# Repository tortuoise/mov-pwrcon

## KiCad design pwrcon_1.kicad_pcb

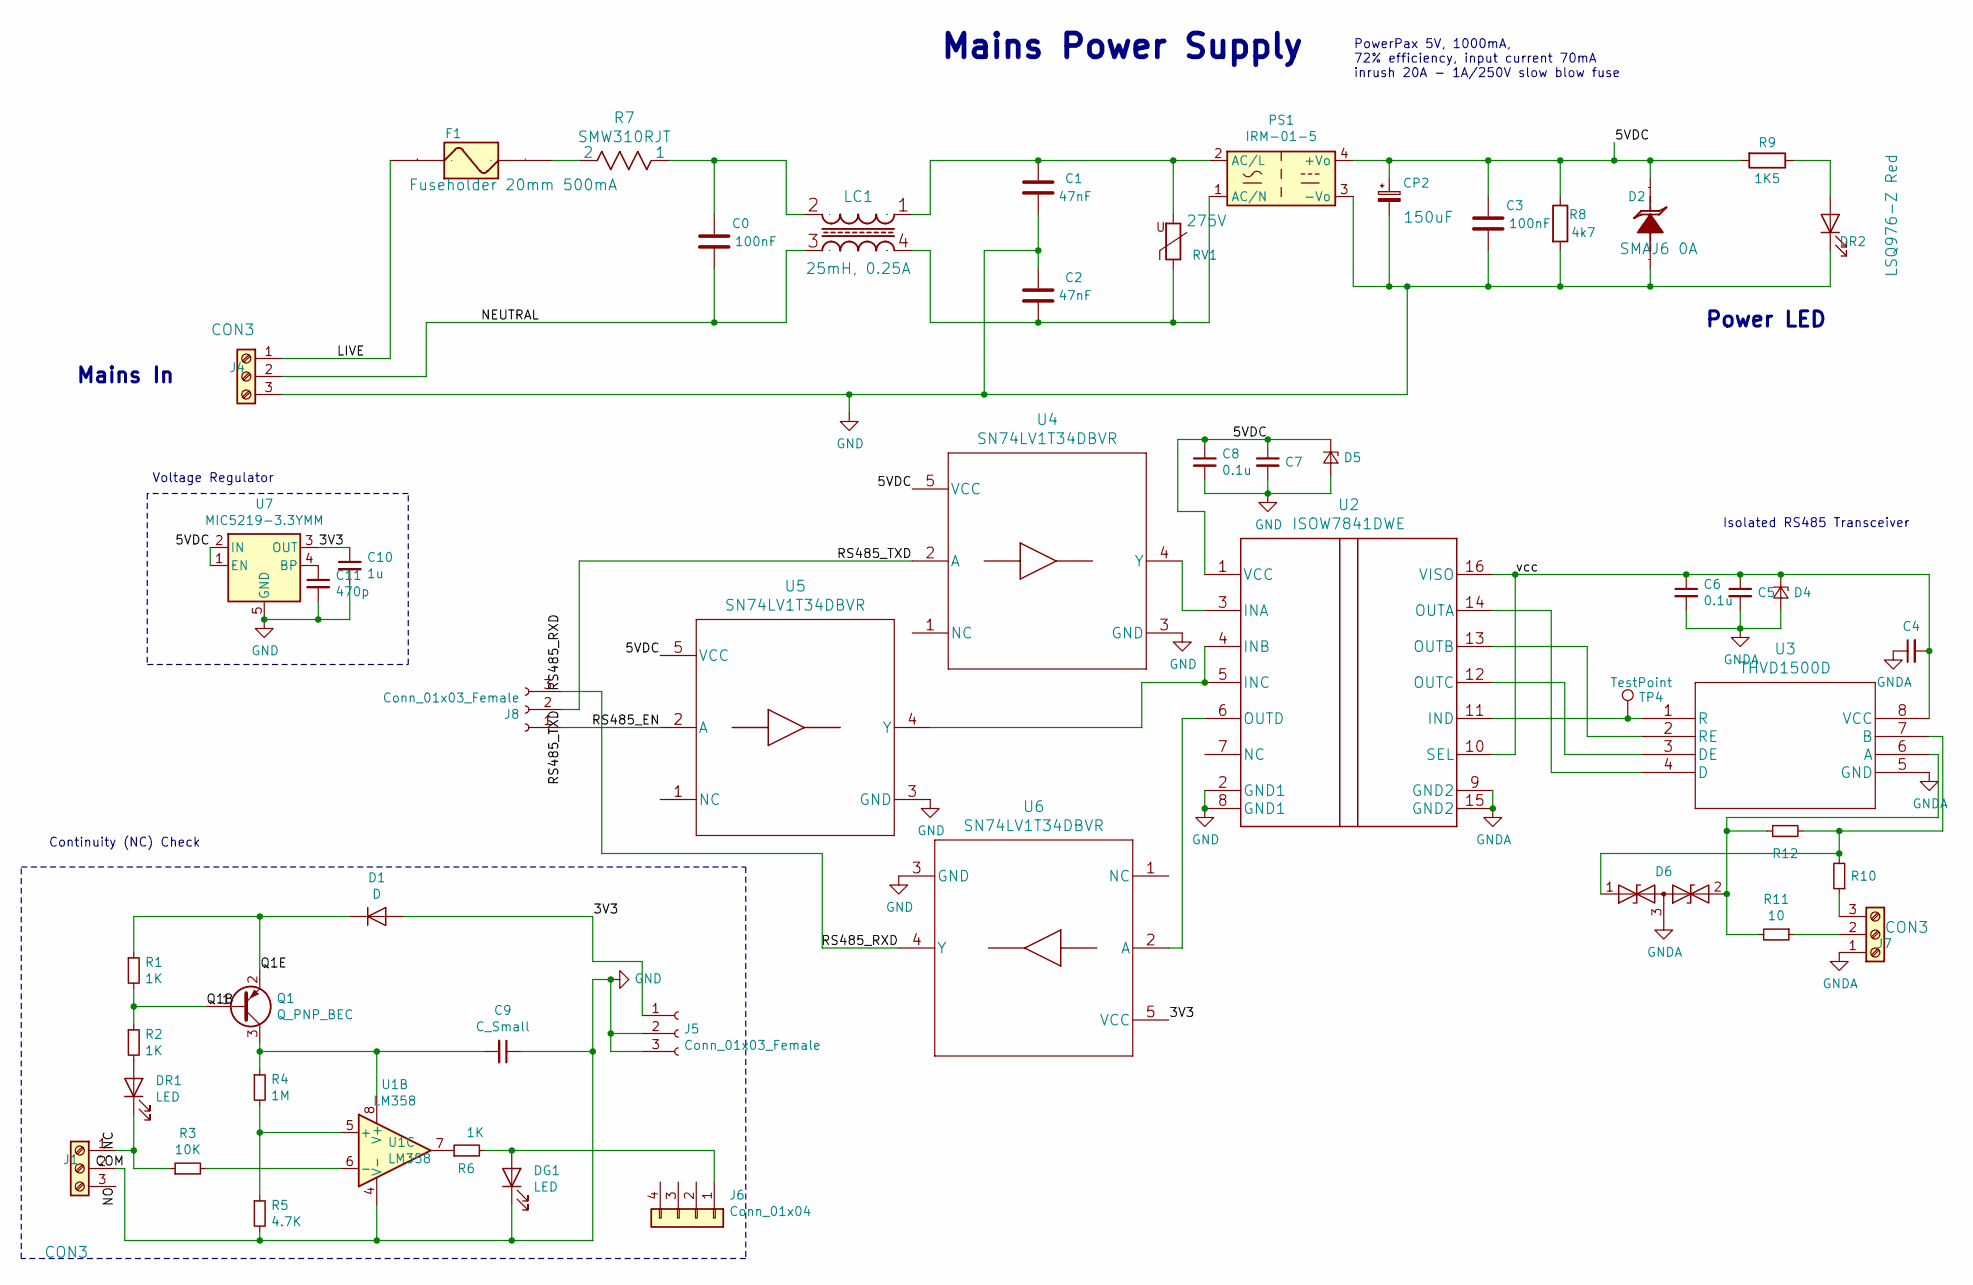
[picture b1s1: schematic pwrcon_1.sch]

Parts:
C0: 100nF; C_Rect_L18.0mm_W5.0mm_P15.00mm_FKS3_FKP3; PartNo ECQU2A104ML
C1, C2: 47nF; C_Rect_L10.0mm_W4.0mm_P7.50mm_MKS4; PartNo BFC233660473
C3: 100nF; C_0603_1608Metric_Pad1.05x0.95mm_HandSolder; MFG Part Num EMK107B7104KAHT
C4, C6, C8: 0.1u; C_0603_1608Metric_Pad1.05x0.95mm_HandSolder; MFG Part Num C0603C104J4RACTU
C5, C7: 10u; C_0603_1608Metric_Pad1.05x0.95mm_HandSolder; MFG Part Num C0603C106M9PACTU
C9: C_Small; C_0603_1608Metric_Pad1.05x0.95mm_HandSolder; MFG Part Num ‎EMK107B7104KAHT‎
C10: 1u; C_0603_1608Metric_Pad1.05x0.95mm_HandSolder
C11: 470p; C_0603_1608Metric_Pad1.05x0.95mm_HandSolder
CP2: 150uF; CP_EIA-7343-20_Kemet-V_Pad2.25x2.55mm_HandSolder; PartNo TRJD157K010R0150 / T495V157M010ATE150
D1: D; D_SOD-123; MFG Part Num BAV16W-7-F
D2: SMAJ6 0A; D_SMA; PartNo SMAJ6.0A
D4, D5: D_Zener_Small; D_SMB_Handsoldering; MFG Part Num 1SMB5919BT3G
D6: CDSOT23-SM712; SOT-23; MFG Part Num CDSOT23-SM712
DG1: LED; LED_0603_1608Metric_Pad1.05x0.95mm_HandSolder; MFG Part Num SML-D12M8WT86
DR1: LED; LED_0603_1608Metric_Pad1.05x0.95mm_HandSolder; MFG Part Num SML-D12V8WT86
DR2: LSQ976-Z Red; LED_0603_1608Metric_Pad1.05x0.95mm_HandSolder; PartNo LS Q976-NR-1
F1: Fuseholder 20mm 500mA; Fuseholder_Cylinder-5x20mm_Schurter_0031_8201_Horizontal_Op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; PartNo 0031.8201
J1, J4: CON3; PhoenixContact_MCV_1,5_3-G-5.08_1x03_P5.08mm_Vertical; MFG Part Num ED365/3
J5, J8: Conn_01x03_Female; PinSocket_1x03_P2.54mm_Vertical
J6: Conn_01x04; PinSocket_1x04_P2.54mm_Vertical
J7: CON3; PhoenixContact_MCV_1,5_3-G-5.08_1x03_P5.08mm_Vertical; PartNo ED365/3
LC1: 25mH, 0.25A; choke_wurth_744862250; PartNo 744862250
PS1: IRM-01-5; Converter_ACDC_MeanWell_IRM-02-xx_THT; MFG Part Num IRM-01-5
Q1: Q_PNP_BEC; SOT-23_Handsoldering; MFG Part Num FMMT718
R1, R2, R6: 1K; R_0603_1608Metric; MFG Part Num ESR03EZPJ102
R3: 10K; R_0603_1608Metric
R4: 1M; R_0603_1608Metric; MFG Part Num RCS06031M00FKEA
R5: 4.7K; R_0603_1608Metric_Pad1.05x0.95mm_HandSolder; MFG Part Num ESR03EZPJ472
R7: SMW310RJT; MFG Part Num SMW310RJT
R8: 4k7; R_0805_2012Metric_Pad1.15x1.40mm_HandSolder; MFG Part Num ERJ-P06J472V
R9: 1K5; R_0603_1608Metric; MFG Part Num ESR03EZPJ152
R10, R11: 10; R_2512_6332Metric_Pad1.52x3.35mm_HandSolder; MFG Part Num CRCW251210R0FKEG
R12: 120; R_0603_1608Metric_Pad1.05x0.95mm_HandSolder; MFG Part Num CRCW0603120RJNEA
RV1: 275V; RV_Disc_D7mm_W4mm_P5mm; PartNo 820572711
TP4: TestPoint; TestPoint_Loop_D1.80mm_Drill1.0mm_Beaded
U1: LM358; DIP-8_W7.62mm
U2: ISOW7841DWE; MFG Part Num ISOW7841D
U3: THVD1500D; MFG Part Num THVD1500DR
U4, U5, U6: SN74LV1T34DBVR; MFG Part Num SN74LV1T34DBVR
U7: MIC5219-3.3YMM; MSOP-8_3x3mm_P0.65mm; MFG Part Num MIC5219-3.3YMM

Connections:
/3V3: C10.1, D1.2 (A), J5.1, U6.5 (VCC), U7.3 (OUT)
/5VDC: C3.2, C7.1, C8.1, CP2.1, D2.1 (CATHODE), D5.1 (K), PS1.4 (+Vo), R8.1, R9.2, U2.1 (VCC), U4.5 (VCC), U5.5 (VCC), U7.1 (EN), U7.2 (IN)
/LIVE: F1.1, J4.1
/NC: DR1.1 (K), J1.1, R3.1
/NEUTRAL: C0.1, J4.2, LC1.3
/Q1B: Q1.1 (B), R1.2, R2.1
/Q1E: D1.1 (K), Q1.2 (E), R1.1
/RS485_EN: J8.1, U5.2 (A)
/RS485_RXD: J8.3, U6.4 (Y)
/RS485_TXD: J8.2, U4.2 (A)
/vcc: C4.2, C5.1, C6.1, D4.1 (K), U2.10 (SEL), U2.16 (VISO), U3.8 (VCC)
GND: C1.1, C2.2, C3.1, C7.2, C8.2, C9.1, C10.2, C11.2, CP2.2, D2.2 (ANODE), D5.2 (A), DG1.1 (K), DR2.1 (K), J1.2, J4.3, J5.2, J5.3, PS1.3 (-Vo), R5.2, R8.2, U1.4 (V-), U2.2 (GND1), U2.8 (GND1), U4.3 (GND), U5.3 (GND), U6.3 (GND), U7.5 (GND), U7.6 (GND), U7.7 (GND), U7.8 (GND)
GNDA: C4.1, C5.2, C6.2, D4.2 (A), D6.3 (common), J7.1, U2.9 (GND2), U2.15 (GND2), U3.5 (GND)
unnamed: C0.2, LC1.2, R7.1
unnamed: C1.2, LC1.1, PS1.2 (AC/L), RV1.2
unnamed: C2.1, LC1.4, PS1.1 (AC/N), RV1.1
unnamed: C9.2, Q1.3 (C), R4.1, U1.8 (V+)
unnamed: C11.1, U7.4 (BP)
unnamed: D6.1 (A1), R10.2, R12.2, U3.7 (B)
unnamed: D6.2 (A2), R11.2, R12.1, U3.6 (A)
unnamed: DG1.2 (A), J6.1, R6.2
unnamed: DR1.2 (A), R2.2
unnamed: DR2.2 (A), R9.1
unnamed: F1.2, R7.2
unnamed: J7.2, R11.1
unnamed: J7.3, R10.1
unnamed: R3.2, U1.6 (-)
unnamed: R4.2, R5.1, U1.5 (+)
unnamed: R6.1, U1.7
unnamed: TP4.1, U2.11 (IND), U3.1 (R)
unnamed: U2.3 (INA), U4.4 (Y)
unnamed: U2.4 (INB), U2.5 (INC), U5.4 (Y)
unnamed: U2.6 (OUTD), U6.2 (A)
unnamed: U2.12 (OUTC), U3.3 (DE)
unnamed: U2.13 (OUTB), U3.2 (RE)
unnamed: U2.14 (OUTA), U3.4 (D)

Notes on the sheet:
Mains Power Supply
PowerPax 5V, 1000mA, 72% efficiency, input current 70mA inrush 20A - 1A/250V slow blow fuse
Mains In
Isolated RS485 Transceiver
Power LED
Voltage Regulator
Continuity (NC) Check

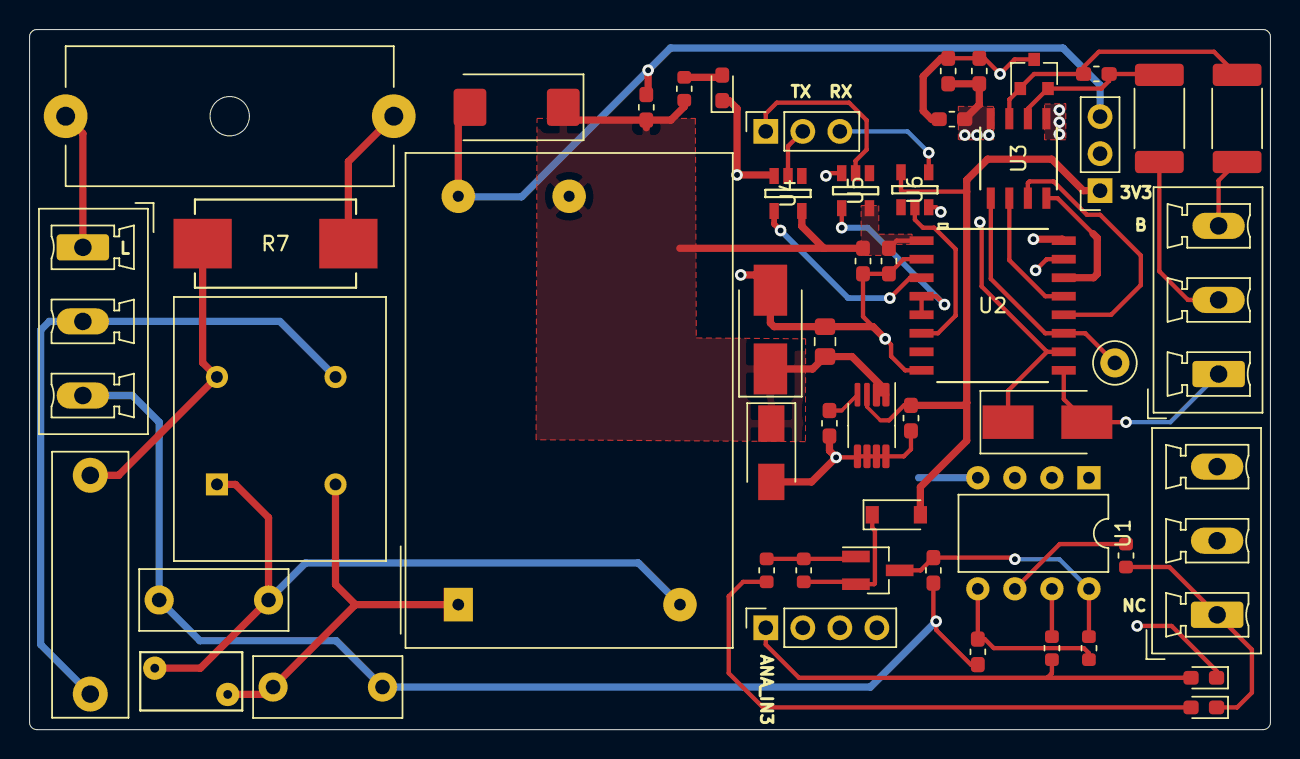
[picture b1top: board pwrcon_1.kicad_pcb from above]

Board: 2 copper layers, 85.1 x 48.0 mm, 52 parts (0 on the bottom side), 36 nets.

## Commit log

2020-01-23 Flipped the transistor so it lines up with footprint
2020-02-06 Added docs directory for datasheets
2020-02-06 Changed pcb file for transistor flip in previous commit. Changed PSU module name in schematic
2020-09-16 Changed module to 5V, added 3V3 regulator and isolated RS485 transceiver, changed to SMD
2020-09-16 Preliminary routing
2020-09-17 More routing, component footprints finalised and missing ones added into repo
2020-09-21 Aisler fab submit
2020-09-22 Flipped varistor and led in schematic (no difference to board), cleaned up project/global footprint libraries
2020-10-05 Added missing 5VDC connection to isolator (isow7841dwe) and created new net vcc between isolator and esd/transceiver(thvd1500d). Changed layout.

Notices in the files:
parts and their libraries:
Copyright 2016 Accelerated Designs. All rights reserved.
